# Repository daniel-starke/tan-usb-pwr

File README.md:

# TAN USB PWR

The TAN USB PWR adapter allows the modification of the KOBIL "TAN Optimus comfort"
to power it directly from USB instead of using batteries.

# Manufacturing

## PCB

Use the following parameters when ordering the PCB. Note that the values
have only been tested with JLCPCB so far. See [gerber files](hw/gerber).
- layers: 2
- base material: FR4
- dimensions: 85.5x24.5mm 
- thickness: 1.6mm
- surface finish: lead free HASL
- impedance control: no
- outer copper weight: 1oz

With no special extras.

## BOM

- 1x [USB 2.0 type C receptacle](https://www.lcsc.com/datasheet/lcsc_datasheet_2410010003_Korean-Hroparts-Elec-TYPE-C-31-M-12_C165948.pdf)
- 1x [0805 200Ω resistor](https://www.lcsc.com/datasheet/lcsc_datasheet_2206010200_UNI-ROYAL-Uniroyal-Elec-0805W8F2000T5E_C17540.pdf)

All parts can be ordered at [LCSC](https://www.lcsc.com) (C165948 and C17540).

## Printing

Print [the cover](3d/TUP-Cover.stl) in the given orientation using the following settings:
- PLA
- layer height: 0.2mm
- infill: 100%
- supports: on base plate only (not at the hole)

Print [the cap](3d/TUP-Cap.stl) in the given orientation using the following settings:
- PLA
- layer height: 0.2mm
- infill: 100%
- supports: none

Hint: Do not use PETG as it tends to be hard to glue.

## Assembly

 1. Solder P1 (USB connector).
 2. Solder R1 (resistor).
 3. Remove the cover and the batteries from "TAN Optimus comfort".
 4. Insert the 8-shaped PCB into the battery slot. Be careful with the orientation (GND at plus, 5V at minus).  
    
 5. Add glue to the back of it.
 6. Insert the 3D printed cover and fasten the screw.  
    
 7. Add glue to the back of it.
 8. Insert the rectangle shaped PCB with the USB connector. Be careful with the orientation and align the holes in the middle correctly.
 9. After the glue dried: Loose the screw and add solder to each of the two holes in the middle to form a connection between the top and the bottom PCB.
10. Cut the excessive part of the pins connecting the top and the bottom PCB.
11. Put the finished PCB assemble into "TAN Optimus comfort".
12. Fasten the screw.  
      
    *Note: The wrong label for 5V and GND seen here were corrected in the final version.*
13. Glue on the 3D printed cap to protect the parts and pads. Or use some hot glue.

Note: The original screw is being reused.

# Technical Background

The "TAN Optimus comfort" is power by two CR2025 in series. Each can provide
between 2 and 3.6 V under load. That means the device should be more or less
capable of being powered from 4 to 7.2 V. As there is most likely a higher lower
end limit to ensure proper function of the device, it should be assumed higher.  
Looking at USB which provides usually something between 4.4 and 5.50 V it fits
well into the voltage expected by this device. That means it is possible to power
this device directly from USB without any additional voltage transformation.  
To ensure that enough power is provided by USB, a Dedicated Charging Port (DCP)
configuration is used. This allows to draw up to 1.5 A. It is negotiated to the
host by placing an up to 200 Ω resistor between the `D+` and `D-` pin of the USB
receptacle. Shorting is also allowed but I suggest to place a proper resistor
value in-between to limit the current that can go through.

# License

See [LICENSE](LICENSE).

# Credits

Credits to madworm for the [mouse bite footprint](https://github.com/madworm/Panelization.pretty).

# Contributions

No content contributions are accepted. Please file a bug report or feature request instead.  
This decision was made in consideration of the used license.

# Disclaimer

This project is not affiliated with KOBIL GmbH, or any of its affiliates.

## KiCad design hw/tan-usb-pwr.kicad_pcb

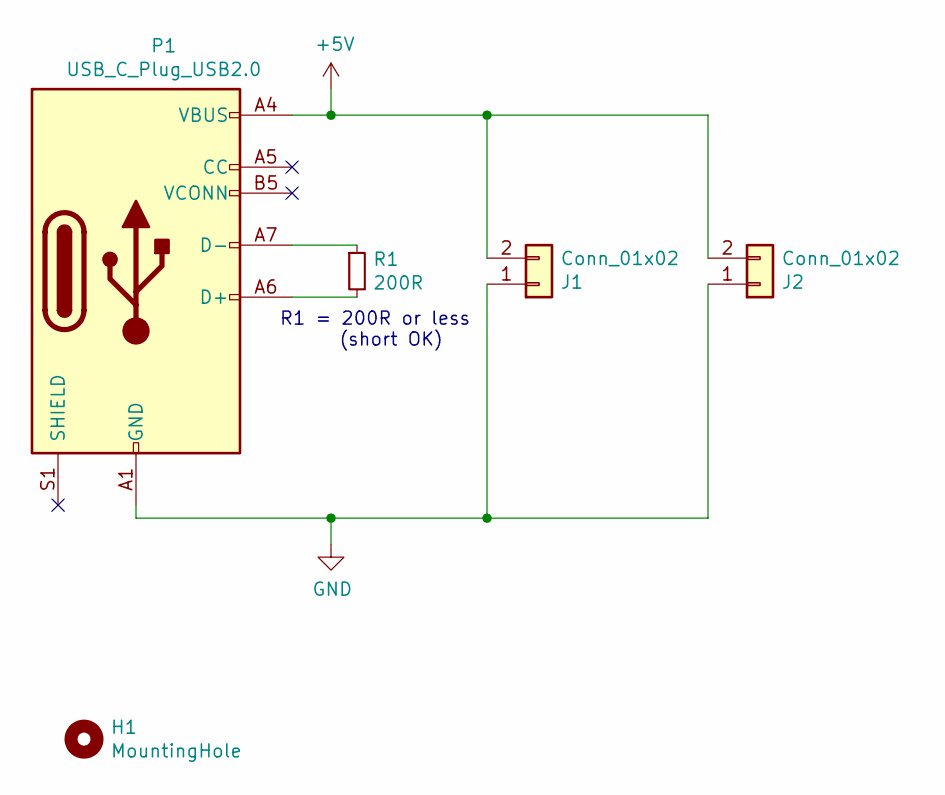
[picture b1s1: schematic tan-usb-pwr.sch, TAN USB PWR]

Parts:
H1: MountingHole; MountingHole_2.1mm
J1, J2: Conn_01x02; PinHeader_1x02_P2.54mm_Vertical
P1: USB_C_Plug_USB2.0; USB_C_HRO_TYPE_C_31_M_12; LCSC C165948
R1: 200R; R_0805_2012Metric_Pad1.15x1.40mm_HandSolder; LCSC C17540

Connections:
+5V: J1.2, J2.2, P1.A4 (VBUS), P1.A9 (VBUS), P1.B4 (VBUS), P1.B9 (VBUS)
GND: J1.1, J2.1, P1.A1 (GND), P1.A12 (GND), P1.B1 (GND), P1.B12 (GND)
unnamed: P1.A6 (D+), R1.2
unnamed: P1.A7 (D-), R1.1

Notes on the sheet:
R1 = 200R or less (short OK)

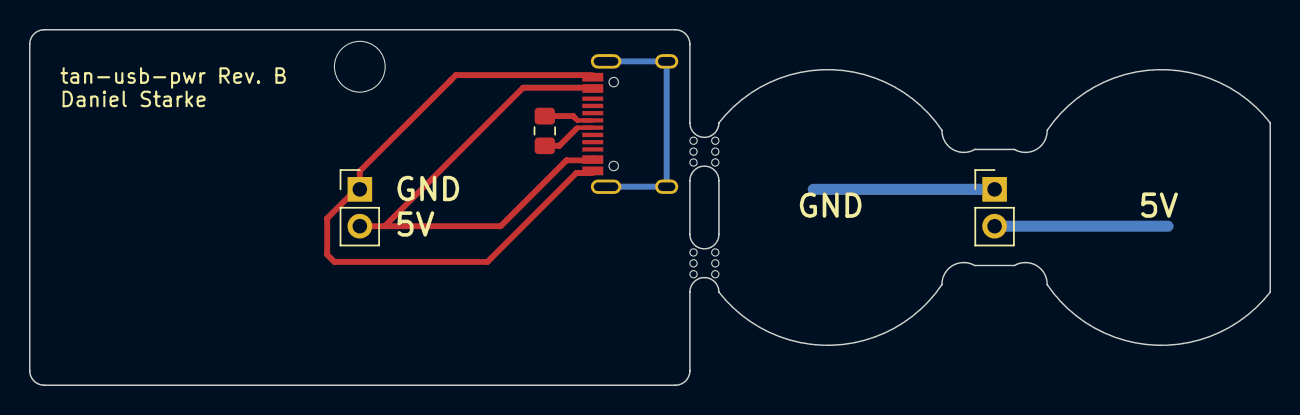
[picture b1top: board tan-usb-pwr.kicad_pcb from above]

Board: 2 copper layers, 85.5 x 24.5 mm, 7 parts (0 on the bottom side), 4 nets.

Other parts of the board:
mouse-bite-2mm-slot, mouse-bite-2mm-slot#2: VAL**; mouse-bite-2mm-slot

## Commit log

2024-12-02 Initial commit.
